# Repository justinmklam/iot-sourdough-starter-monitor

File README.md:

# IoT Sourdough Starter Monitor

Internet connected smart lid for sourdough starter. Tracks fermentation with distance, temperature, and humidity sensors, and publishes data to the cloud for further data logging and analysis.

Interested in more details? Read the full story on [justinmklam.com](https://www.justinmklam.com/posts/2021/02/levain-monitor/)!

<p align="center">
    <br>
    <i>Sourdough starter monitor (left), web application to view the logged data (right).</i>
</p>

<p align="center">
    <br>
    <i>Three modes of operation: Max rise and time, graph, stats for nerds.</i>
</p>

<p align="center">
    <br>
    <i>Selecting, viewing, and downloading data for a given feeding session.</i>
</p>

## Hardware

- NodeMCU ESP8266 (aka NodeMCU 1.0 ESP-12E)
- DHT22 Temperature and humidity sensor
- VL6180X Time of flight distance sensor
- SSD1306 Monochrome 128x32 I2C OLED display

<p align="center">
    <br>
    <i>3D printed enclosure (designed in Fusion 360).</i>
</p>

<p align="center">
    <br>
    <i>PCB schematic and layout (designed in KiCad).</i>
</p>

<p align="center">
    <br>
    <i>Assembled PCB.</i>
</p>

## Software

AWS is used as the cloud backend. Data flow is as follows:

- ESP8266 sends sensor data over MQTT
- Kinesis Firehose receives data
- Lambda function puts data from Firehose to S3 on data receive event
- Web app queries S3 data via Athena

## Getting Started

### PlatformIO

This project is built using PlatformIO v5.1.0. To build:

```bash
# Build
pio run

# Build and upload
pio run -t upload
```

To view the serial monitor:

```bash
pio device monitor -b 115200
```

To run the tests:

```bash
# Run tests on device
pio test

# Run tests locally
pio test -e native
```

## Heroku

To deploy the web app to Heroku:

```
git subtree push --prefix webapp heroku master
```

## AWS IoT Certificates

Convert the certificates from AWS to `.der` files, then place them in `data/` (within the project directory).

```bash
openssl x509 -in xxx-certificate.pem.crt -out cert.der -outform DER
openssl rsa -in xxx-private.pem.key -out private.der -outform DER
openssl x509 -in AmazonRootCA1.pem -out ca.der -outform DER
```

Use the following command to upload the files to the SPIFFS filesystem:

```bash
pio run -t uploadfs
```

Alternatively, you may use the [arduino-esp8266fs-plugin](https://github.com/esp8266/arduino-esp8266fs-plugin) to upload the files.

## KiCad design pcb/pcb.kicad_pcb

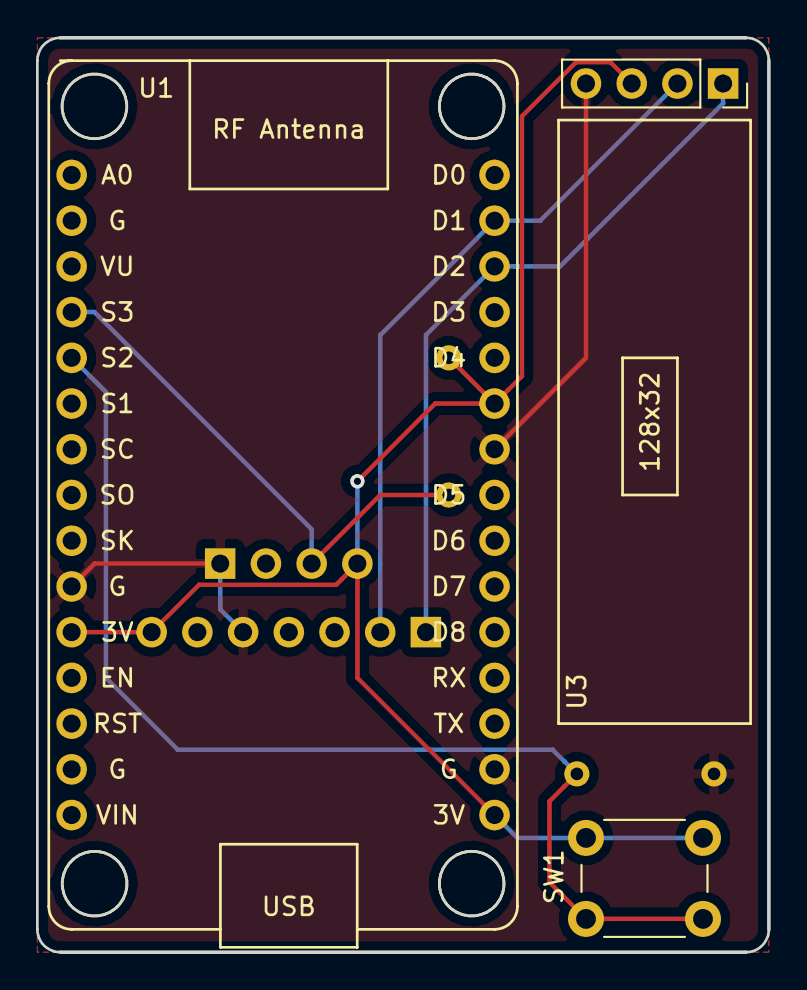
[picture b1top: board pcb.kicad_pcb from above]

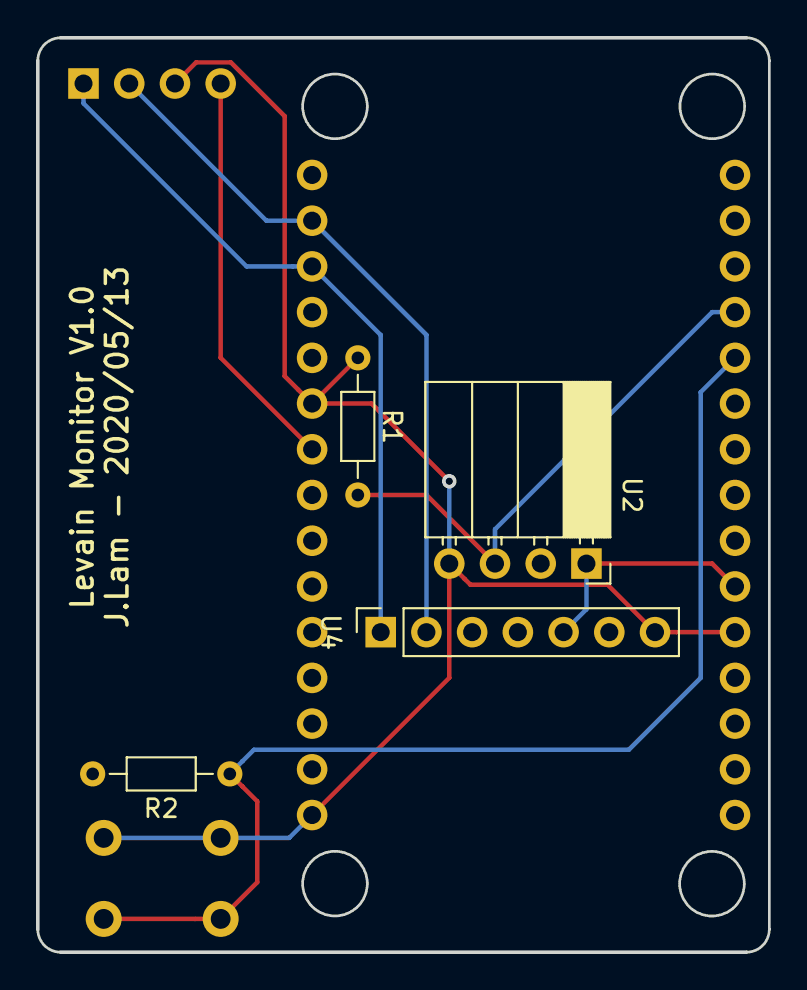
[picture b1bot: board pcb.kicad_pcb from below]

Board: 2 copper layers, 40.6 x 50.8 mm, 7 parts (4 on the bottom side), 6 nets.

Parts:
R1, R2: 10K; R_Axial_DIN0204_L3.6mm_D1.6mm_P7.62mm_Horizontal
SW1: SW_Push; SW_PUSH_6mm
U1: NodeMCU1.0(ESP-12E); ESP12F-Devkit-V3
U2: DHT22; PinSocket_1x04_P2.54mm_Horizontal
U3: SSD1306_OLED_128x32; SSD1306_Adafruit_128x32
U4: VL6180X_Adafruit

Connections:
3v3: R1.1, SW1.1, U1.11, U1.16, U1.25, U2.4, U3.3, U4.7
GND: R2.2, U1.10, U1.17, U1.24, U2.1, U3.4, U4.5
unnamed: R1.2, U1.4, U2.3
unnamed: R2.1, SW1.2, U1.5
SCL: U1.29, U3.2, U4.2
SDA: U1.28, U3.1, U4.1

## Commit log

2020-04-19 Add README
2020-04-19 Initial commit of VL6180X/SSD1306 demo
    From examples repository
2020-04-20 Add working example of device shadow update
2020-04-20 Add AWS IoT libraries to README
2020-04-20 Create gitignore
2020-04-20 Remove wifi credentials from secrets.h
2020-04-20 Use pubsub client instead of mqtt
    Library is more widely used
2020-04-20 Refactor; remove ESP32 references
2020-04-20 Reduce delay in setup()
2020-04-20 Refactor sendData to be more generic
2020-04-20 Remove ArduinoJSON library dependency
2020-04-20 Rename callback function
2020-04-20 Minor changes to device shadow update
2020-04-20 Rename TIME_ZONE to UTC_OFFSET
2020-04-20 Clean up connectToWifi function; rename
2020-04-20 Update README with version numbers
2020-04-20 Add vscode to gitignore
2020-04-20 Load certificates from SPIFFS instead of secrets.h
2020-04-22 Publish to data topic for firehose injestion
    Also bring back ArduinoJson since it simplifiies message creation
2020-04-22 Add manifest.json for kinesis firehose
2020-04-26 Refactor AWS and NTP into separate classes
2020-04-26 Replace ntp global defines with function args
2020-04-26 Replace global defines with explicit setters
2020-04-26 Add methods to subscribe and update device shadow
2020-04-26 Remove commented out global variables
2020-04-26 Only check subscribe topic if not null
    Otherwise stack overflow crash
2020-04-26 Minor edits to certificate SPIFF log messages
2020-04-26 Add comment about UTC magic variable
2020-04-26 Format aws.h and aws.cpp
2020-04-26 Capitalize AWS and NTP filenames
2020-04-26 Move hardcoded publish message out of function
2020-04-26 Add option to load keys from secrest.h instead of SPIFFS
2020-04-26 Remove unused secret definition; add pragma once
2020-04-26 Reorder AWS methods
2020-04-26 Rename NTP config time function
2020-04-26 Refactor SPIFFS certificate load method
2020-04-26 Add pointer checks for setters
    Otherwise stack crash occurs
2020-04-26 Refactor get current ASCII time method
2020-04-28 Add DS_Store to gitignore
2020-04-28 Initial commit of MetricsGraphics.js files
2020-04-28 Working example with MetricsGraphics.js
2020-04-29 Add linked zoom to graphs, change colours
2020-04-29 Integrate bootstrap page template
    Now graphs and page content are responsive
2020-04-29 Add date picker
2020-04-30 Initial commit with flask
2020-04-30 WIP: Add get data route for pandas dataframe
2020-04-30 Move javascript from index.html to separate file
2020-05-02 Move plotting javascript to separate file
2020-05-02 Create js/css subdirectories
2020-05-02 Add pyc to gitignore
2020-05-02 Add .env file
2020-05-02 Add date range picker callback
2020-05-02 Send date request to flask
2020-05-02 Refactor charts
2020-05-03 Update plots from request to backend
2020-05-03 Refactor construction of data out
2020-05-03 Aesthetic improvements
    Replace title with legend, change placeholder texts, etc.
2020-05-03 Update author
2020-05-03 Clean up index.html
2020-05-03 Minify css and js
2020-05-03 Add function to download current data
2020-05-11 Initial commit of pcb
2020-05-12 Add kicad backup files to gitignore
2020-05-12 First PCB revision complete
2020-05-12 Fix untracked files already in repo
2020-05-12 Add board outline
2020-05-12 Move sensors down; fix routing
2020-05-12 Add push button
2020-05-12 Correct display footprint to right size
2020-05-12 Use the right ESP8266 footprint
2020-05-12 Add gerbers and drill table
2020-05-12 Add zip files to gitignore
2020-05-13 Add exposed FR4 to mounting holes
2020-05-13 Add ground plane
2020-05-13 Minor changes before gerber export
2020-05-13 Update gerbers
2020-05-13 Update schematic title block
2020-05-13 Export schematic to PDF
2020-05-14 Fix hole sizes on ESP8266 footprint
2020-05-14 Export gerbers
2020-05-14 Fix track/pad clearance after hole resize
2020-05-30 Add VL6180X sensor to AWS
2020-05-30 Add DHT sensor to AWS
2020-05-30 Add temp/humidity to display
2020-05-30 Set NTP get timestamp to static
2020-05-30 [bugfix] Timestamp now doesn't go to null after 5 calls
2020-05-30 Change publish interval to every minute
2020-06-09 Add media content to README
2020-06-09 Add software description to README
2020-06-09 Fix web app gif
    Originally cropped at 5 seconds for some reason
2020-06-09 Fix punctuation in README
2020-11-20 Rename arduino project directory
2020-11-20 Rename ino file
2020-11-20 Restructure to platformio project
2020-11-20 Add external libraries
2020-11-20 Move headers to include directory
2020-11-20 Fix platform and library versions
2020-11-20 Update README for platformio build instructions
2020-11-20 Enable offline mode
2020-11-20 Add data/ directory for SPIFFS files
2020-11-20 Move AWS and NTP files to lib/
2020-11-20 Add test framework
2020-11-20 Show n/a instead of blank screen when out of range
2020-11-21 Remove manifest.json
2020-11-21 Add mypy_cache to gitignore
2020-11-21 Add pyathena demo
2020-11-21 Add AWS_PROFILE to webapp/.env
2020-11-22 Add task scheduler library
2020-11-22 Refactor measure and display to tasks
2020-11-22 Refactor measurements to struct
2020-11-22 Refactor measurements and display tasks into separate files
2020-11-22 Refactor iot to separate task
2020-11-22 Formatting
2020-11-22 Remove globals.h
2020-11-22 Rename .ino file to main.cpp
2020-11-23 Add user button task
2020-11-23 Add debounce setter
2020-11-23 Differentiate short and long button press
2020-11-24 Add logic for while button is being pressed
2020-11-24 Add user states
2020-11-24 Add state getter and setter
2020-11-24 Rename button.c to userinput.c
2020-11-24 Rename button task to userinput task
2020-11-24 Add states to display.cpp
2020-11-24 Add jar height calibration mode
2020-11-24 Add monitoring state
2020-11-26 Remove arbitrary state change
2020-11-26 Properly calculate rise percentage
2020-11-26 Actually fix rise height percent calculation
2020-11-26 Show rise percent instead of absolute height
2020-11-27 Add EasyButton library
2020-11-27 Add button callbacks
2020-11-27 Replace EasyButton with OneButton
    Handles single and double click at the same time
2020-11-27 Increase user input loop frequency
    Better performance for double click responsiveness
2020-11-27 Use OneButton copy instead of library manager
2020-11-27 Switch behaviour of clicks and long press
2020-11-27 Only enter calibration state if not monitoring
2020-11-27 Don't include iot.h if iot isn't enabled
2020-11-27 Add display states
2020-11-27 Populate advanced dashboard; fix floats/ints
2020-11-27 Simplify default display state
2020-11-27 Add basic plotting of live data
2020-12-07 Plot rise hight as a positive number
2020-12-07 Add circular buffer library
2020-12-07 Add rise height to circular buffer
2020-12-07 Plot rise height from circular buffer
2020-12-07 Rolling window plot of rise percentage (with autoscaling)
2020-12-07 Clear buffer for each new session
2020-12-07 Keep track of time since maximum height
2020-12-07 Refactor max rise time variables
2020-12-07 Show max rise time on advanced display
2020-12-07 Show max rise and time on main screen
2020-12-07 Show rise percent in bottom right corner of graph
2020-12-08 Show time since max instead of current rise
2020-12-08 Refactor display state to be in display.cpp
2021-01-01 Store temperature measurements in buffer
2021-01-01 Add temperature graph
2021-01-02 Add session and device id to measurements
2021-01-02 Enable IoT thread, extend task delay to 10s
2021-01-02 Update published message with measurements
2021-01-02 Only publish messages when monitoring, but need to update shadow to keep connection alive
2021-01-02 Use time in shadow instead
2021-01-02 Remove unused variable
2021-01-02 Only update the shadow when not publishing
2021-01-02 Display more useful mqtt error in serial
2021-01-02 Limit adding measurements to buffer
2021-01-02 Add wifi connection timeout
2021-01-02 Use onboard LED to show wifi status
2021-01-02 Don't publish messages if offline
2021-01-02 Use a random number for the session ID
2021-01-18 Add 3D models to components and export STEP file of PCB
2021-01-18 Initial commit of enclosure files
2021-01-20 Save jar height to eeprom
2021-01-20 Only commit to EEPROM on state change
2021-01-20 Only flash LED when sending message to aws
2021-01-20 Change C to J for jar in display
2021-01-21 Change graph to show every 5 mins instead of 15 mins
2021-01-21 Remove decimal places on main screen
2021-01-21 Show rise duration on graph screen instead
2021-01-21 Add pyathena[pandas] to requirements
2021-01-21 Update SQL query to get list of unique sessions
2021-01-21 Add second query for getting session data
2021-01-21 Refactor constants to variables
2021-01-21 Refactor athena database queries
2021-01-21 Rename athena.py to database.py
2021-01-21 Link charts to athena database
2021-01-21 Move javascript to plot.js
2021-01-21 Load charts with latest data
2021-01-21 Replace legend with y axis labels
2021-01-21 Reduce bottom margin and zoom in page
2021-01-21 Remove zoom since it messes with graph zoom
2021-01-21 Update web app gif
2021-01-21 Add UTC to PDT time offset
2021-01-21 Format datestamp to be more human readable
2021-01-21 Disable dropdown when loading
2021-01-21 Add recording icon, center text
2021-01-21 Show time to rise on graph
2021-01-21 Improve splash screen
2021-01-21 Add offline mode, reconnect to wifi if disconnected
2021-01-21 Remove unused string wrapper
2021-01-21 Show error if publish isn't successful
2021-01-21 Reconnect to MQTT if disconnected
2021-01-21 Increase wifi timeout
2021-01-21 Refactor LED on/off
2021-01-21 Try reconnecting to mqtt if publish doesn't succeed
    Also remove shadow update now that mqtt can reconnect if disconnected
2021-01-22 Fix initialize IoT
2021-01-22 Add timeout for mqtt connection and delay
    Hopefully this fixes soft wdt reset issue
2021-01-22 Add mqtt loop so it stays connected
2021-01-22 Refactor publish interval
2021-01-22 Remove publish retries since it doesn't work
2021-01-22 Minor improvements to print publish message
2021-01-22 Move IoT task up in priority, decrease loop time to 10ms
    Seems to be working more reliably...
2021-01-22 Increase publish interval from 10s to 60s
2021-01-22 Save session id to eeprom instead of using random number
    Turns out the random number isn't all that random!
2021-01-22 Move start of monitoring session to state change
2021-01-22 Remove commented out code
2021-01-22 Autoformat code
2021-01-22 Remove unused imports
2021-01-22 Authenticate aws through env vars
2021-01-22 Add env file to gitignore
2021-01-22 Remove env file from repo
2021-01-22 Add Procfile and gunicorn for heroku
2021-01-22 Add heroku deployment command to README
2021-01-22 Clean up README
2021-01-22 Use sessions instead of global variables
2021-01-22 Make unique filename
2021-01-22 Add caching to database queries
2021-01-22 Drop redundant time column
2021-01-22 Show loading charts
2021-01-22 Get sessions on server start to load cache
2021-01-22 Refactor to application factory
2021-01-22 Save data to pickle file instead of session cookie
    Dataframe was too big to fit inside the cookie
2021-01-22 Show data loading error if response fails
2021-01-22 Fix Procfile with create_app()
2021-01-23 Update LICENSE
2021-01-29 Minor changes to enclosure
2021-01-30 Show icon if not connected to wifi
2021-01-30 Manually center rise percent text
2021-02-16 Add media to README
2021-02-18 Initial commit of analysis script
2021-02-18 Save plot figures
2021-02-18 Add notebook
2021-02-18 Update plots, add r2 and p values
2021-02-20 Add timeseries plots for temp, humidity
2021-02-20 Update plots
2021-02-20 Remove unused analysis script
2021-02-20 Clean notebook output
2026-02-03 Add step file of full model
